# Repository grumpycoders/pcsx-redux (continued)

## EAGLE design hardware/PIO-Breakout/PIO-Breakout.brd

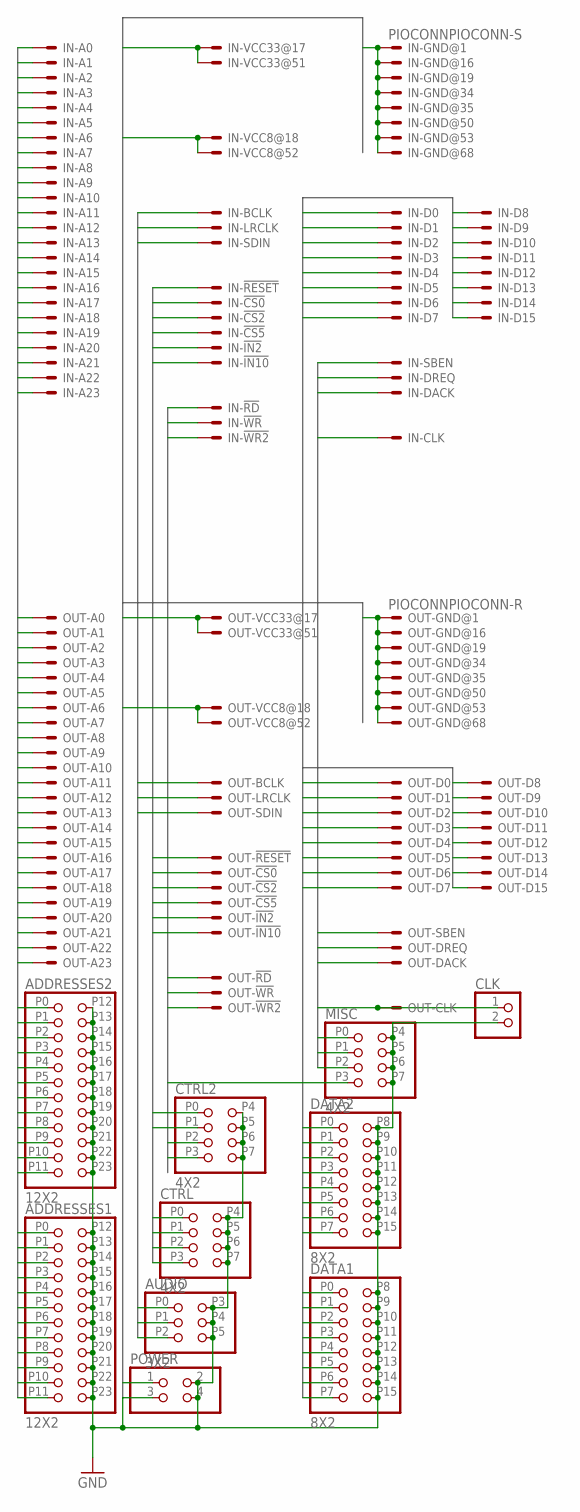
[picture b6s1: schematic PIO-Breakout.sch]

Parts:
ADDRESSES1, ADDRESSES2: 12X2
AUDIO: 3X2
CLK: PINHD-1X2; 1X02
CTRL, CTRL2: 4X2
DATA1, DATA2: 8X2
IN: PIOCONNPIOCONN-S; PIOCONN
MISC: 4X2
OUT: PIOCONNPIOCONN-R; PIOCONN-R
POWER: PINHD-2X2; 2X02

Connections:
+3V3: IN.17, IN.51, OUT.17, OUT.51, POWER.3
+8V: IN.18, IN.52, OUT.18, OUT.52, POWER.1
A0: ADDRESSES1.P11, IN.14, OUT.14
A1: ADDRESSES2.P11, IN.48, OUT.48
A2: ADDRESSES1.P10, IN.15, OUT.15
A3: ADDRESSES2.P10, IN.49, OUT.49
A4: ADDRESSES1.P9, IN.20, OUT.20
A5: ADDRESSES2.P9, IN.54, OUT.54
A6: ADDRESSES1.P8, IN.21, OUT.21
A7: ADDRESSES2.P8, IN.55, OUT.55
A8: ADDRESSES1.P7, IN.22, OUT.22
A9: ADDRESSES2.P7, IN.56, OUT.56
A10: ADDRESSES1.P6, IN.23, OUT.23
A11: ADDRESSES2.P6, IN.57, OUT.57
A12: ADDRESSES1.P5, IN.24, OUT.24
A13: ADDRESSES2.P5, IN.58, OUT.58
A14: ADDRESSES1.P4, IN.25, OUT.25
A15: ADDRESSES2.P4, IN.59, OUT.59
A16: ADDRESSES1.P3, IN.26, OUT.26
A17: ADDRESSES2.P3, IN.60, OUT.60
A18: ADDRESSES1.P2, IN.27, OUT.27
A19: ADDRESSES2.P2, IN.61, OUT.61
A20: ADDRESSES1.P1, IN.28, OUT.28
A21: ADDRESSES2.P1, IN.62, OUT.62
A22: ADDRESSES1.P0, IN.29, OUT.29
A23: ADDRESSES2.P0, IN.63, OUT.63
BCLK: AUDIO.P2, IN.33, OUT.33
CLK: CLK.1, IN.32, OUT.32
CS0: CTRL.P0, IN.4, OUT.4
CS2: CTRL.P1, IN.39, OUT.39
CS5: CTRL2.P0, IN.65, OUT.65
D0: DATA1.P7, IN.6, OUT.6
D1: DATA2.P7, IN.40, OUT.40
D2: DATA1.P6, IN.7, OUT.7
D3: DATA2.P6, IN.41, OUT.41
D4: DATA1.P5, IN.8, OUT.8
D5: DATA2.P5, IN.42, OUT.42
D6: DATA1.P4, IN.9, OUT.9
D7: DATA2.P4, IN.43, OUT.43
D8: DATA1.P3, IN.10, OUT.10
D9: DATA2.P3, IN.44, OUT.44
D10: DATA1.P2, IN.11, OUT.11
D11: DATA2.P2, IN.45, OUT.45
D12: DATA1.P1, IN.12, OUT.12
D13: DATA2.P1, IN.46, OUT.46
D14: DATA1.P0, IN.13, OUT.13
D15: DATA2.P0, IN.47, OUT.47
DACK: IN.36, MISC.P1, OUT.36
DREQ: IN.3, MISC.P2, OUT.3
GND: ADDRESSES1.P12, ADDRESSES1.P13, ADDRESSES1.P14, ADDRESSES1.P15, ADDRESSES1.P16, ADDRESSES1.P17, ADDRESSES1.P18, ADDRESSES1.P19, ADDRESSES1.P20, ADDRESSES1.P21, ADDRESSES1.P22, ADDRESSES1.P23, ADDRESSES2.P12, ADDRESSES2.P13, ADDRESSES2.P14, ADDRESSES2.P15, ADDRESSES2.P16, ADDRESSES2.P17, ADDRESSES2.P18, ADDRESSES2.P19, ADDRESSES2.P20, ADDRESSES2.P21, ADDRESSES2.P22, ADDRESSES2.P23, AUDIO.P3, AUDIO.P4, AUDIO.P5, CLK.2, CTRL.P4, CTRL.P5, CTRL.P6, CTRL.P7, CTRL2.P4, CTRL2.P5, CTRL2.P6, CTRL2.P7, DATA1.P8, DATA1.P9, DATA1.P10, DATA1.P11, DATA1.P12, DATA1.P13, DATA1.P14, DATA1.P15, DATA2.P8, DATA2.P9, DATA2.P10, DATA2.P11, DATA2.P12, DATA2.P13, DATA2.P14, DATA2.P15, IN.1, IN.16, IN.19, IN.34, IN.35, IN.50, IN.53, IN.68, MISC.P4, MISC.P5, MISC.P6, MISC.P7, OUT.1, OUT.16, OUT.19, OUT.34, OUT.35, OUT.50, OUT.53, OUT.68, POWER.2, POWER.4
IN2: CTRL2.P1, IN.31, OUT.31
IN10: CTRL.P2, IN.37, OUT.37
LRCLK: AUDIO.P1, IN.66, OUT.66
RD: CTRL2.P2, IN.30, OUT.30
RESET: CTRL.P3, IN.2, OUT.2
SBEN: IN.5, MISC.P0, OUT.5
SDIN: AUDIO.P0, IN.67, OUT.67
WR: CTRL2.P3, IN.64, OUT.64
WR2: IN.38, MISC.P3, OUT.38

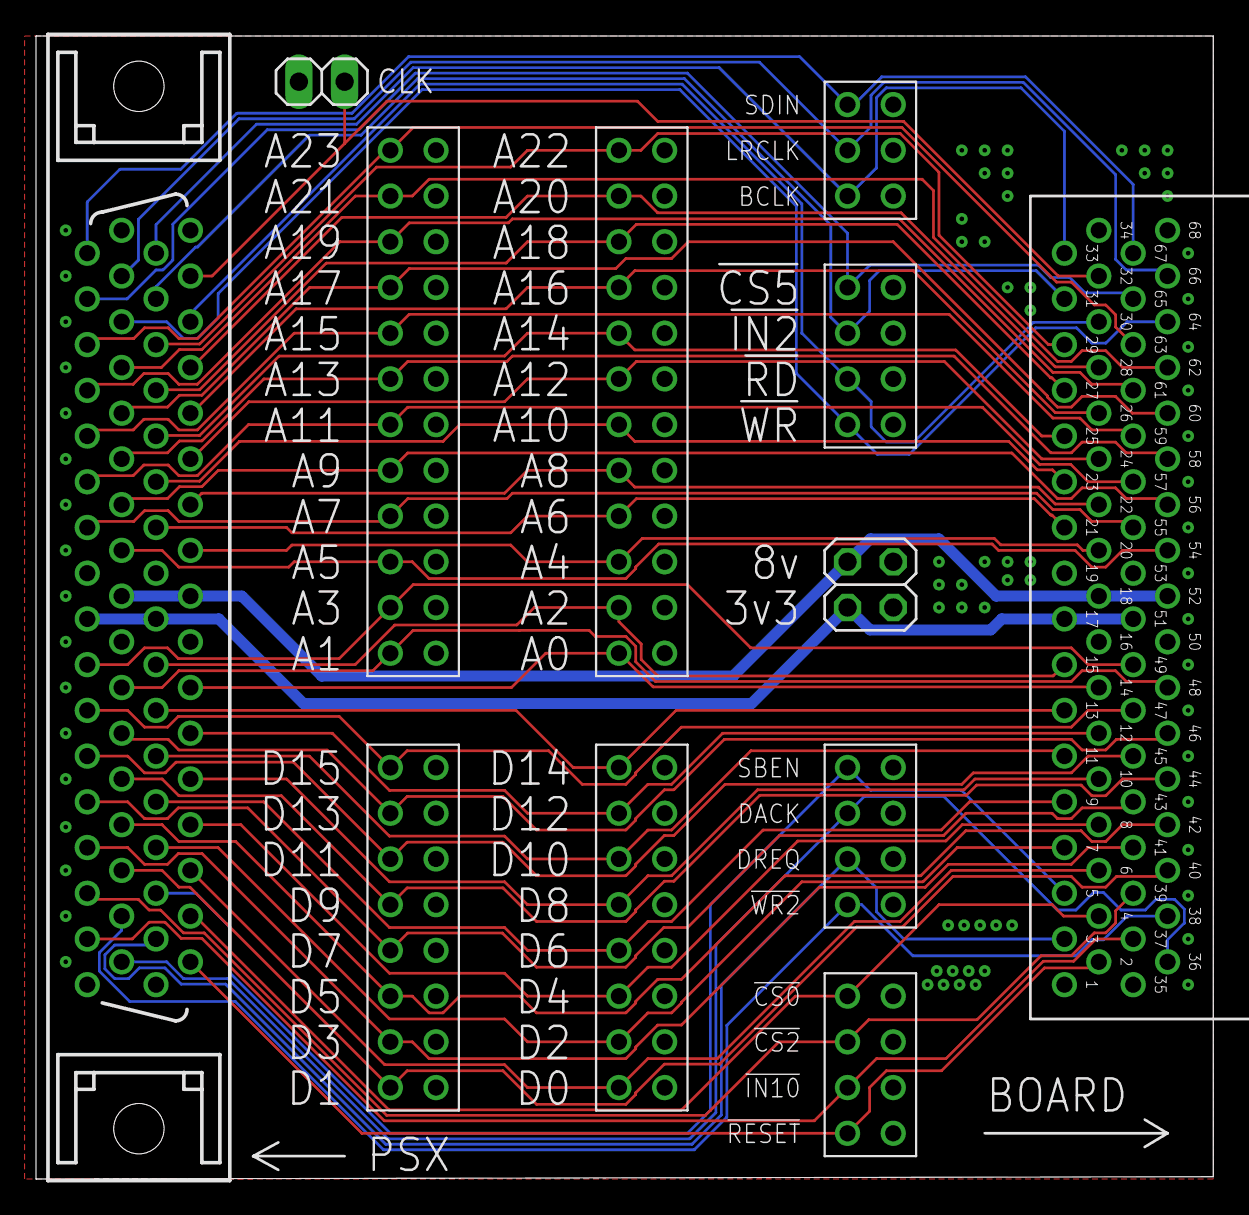
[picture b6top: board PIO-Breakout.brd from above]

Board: 2 copper layers, 65.4 x 63.5 mm, 12 parts (1 on the bottom side), 59 nets.

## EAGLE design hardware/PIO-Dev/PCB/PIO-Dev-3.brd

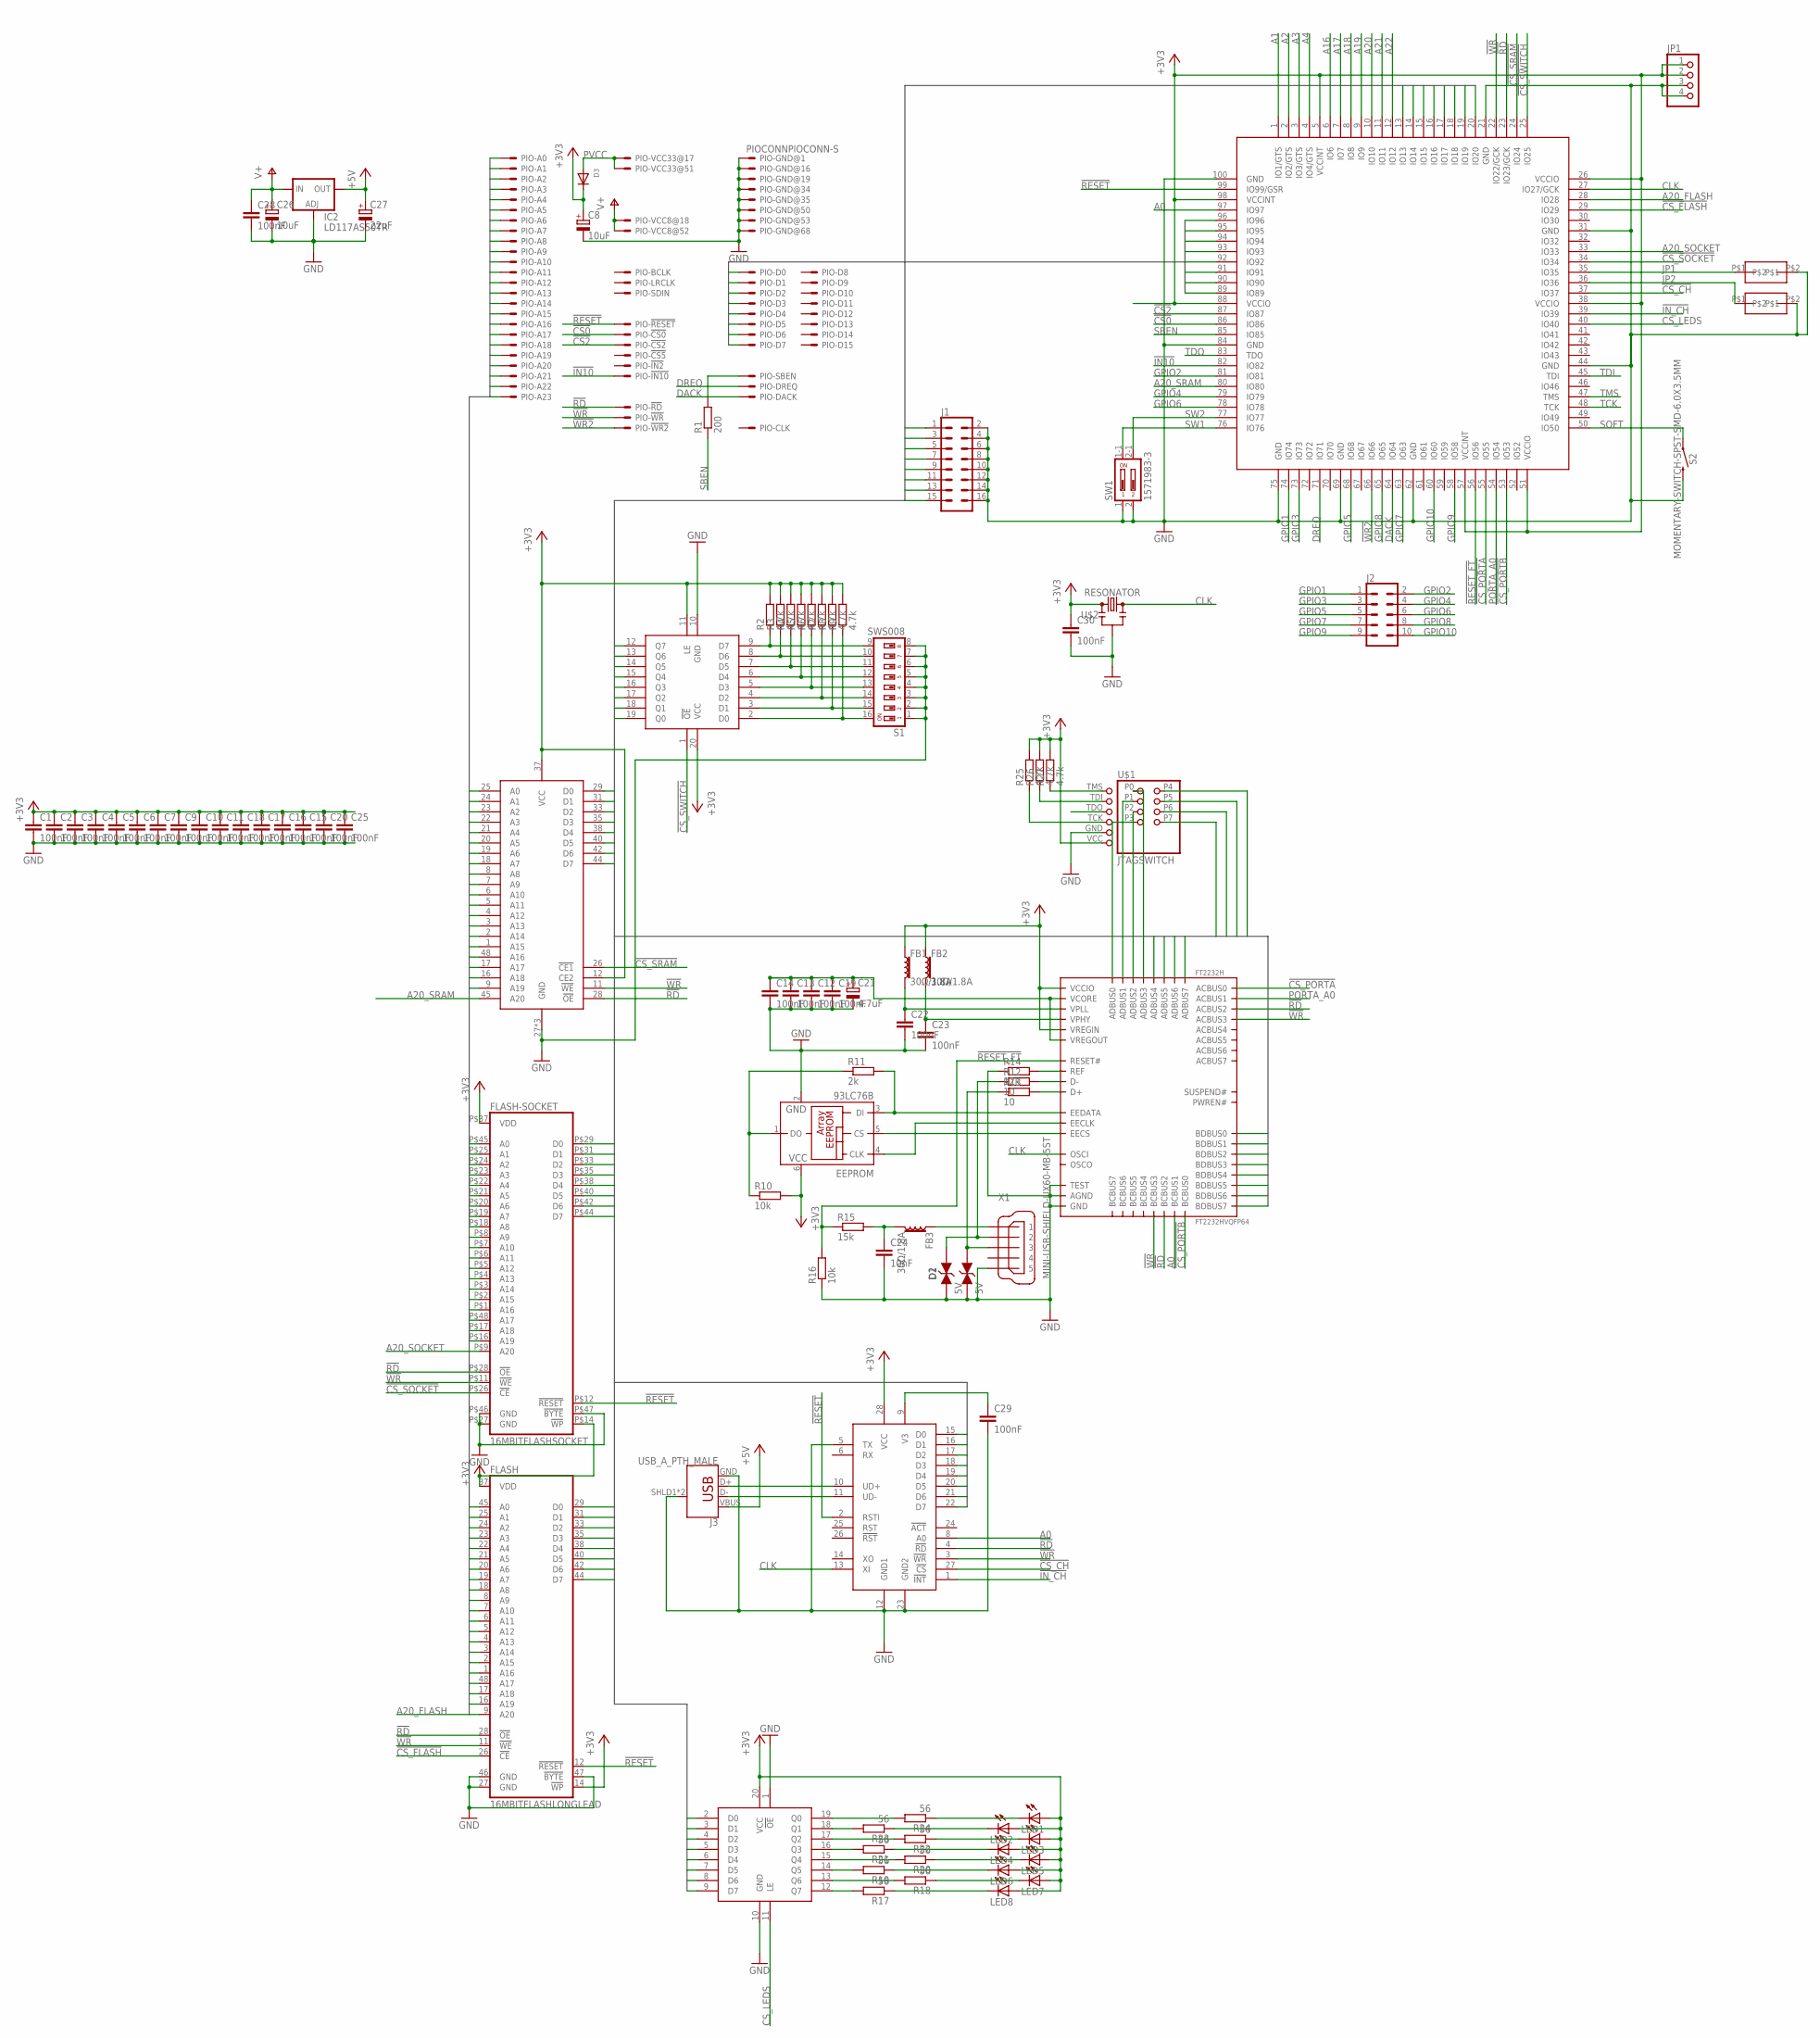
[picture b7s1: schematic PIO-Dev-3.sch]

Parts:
C1, C2, C3, C4, C5, C6, C7, C9, C10, C11, C25, C29: 100nF; C0402K
C8, C26: 10uF; A/3216-18W
C12, C13, C14, C15, C16, C17, C18, C19, C20, C22, C23, C28, C30: 100nF; C0603K
C21: 4.7uF; A/3216-18W
C24: 10nF; C0402K
C27: 22uF; A/3216-18W
CH: CH375B; SOP28-LL
CPLD: XC95144XL-100; TQFP100
D1, D2: 5V; WE-VE_0603
D3: DIODESOD-123; SOD-123
EEPROM: 93LC76B; SOT23-6
FB1, FB2, FB3: 30Ω/1.8A; 0603
FLASH: 16MBITFLASHLONGLEAD; TSOP48-LL
FLASH-SOCKET: 16MBITFLASHSOCKET; TSOP48-ADAPTER
FT2232H: FT2232HVQFP64; VQFP64
IC2: LD117AS50TR; SOT223
J1: CONN_08X2SHD_SMD; 2X8-SHROUDED_SMD
J2: CONN_05X2SHD_SMD; 2X5-SHROUDED_SMD
J3: USB_A_PTH_MALE; USB-A-H
JP1: PINHD-1X4; 1X04
LED1, LED2, LED3, LED4, LED5, LED6, LED7, LED8: LEDCHIPLED_1206; CHIPLED_1206
LEDS: 74LVC573APW; TSSOP20-LL
PIO: PIOCONNPIOCONN-S; PIOCONN
R1: 200; R0402
R2, R3, R4, R5, R6, R7, R8, R9, R25, R26, R27: 4.7k; R0402
R10, R16: 10k; R0402
R11: 2k; R0402
R12, R13: 10; R0402
R14: 12k; R0402
R15: 15k; R0402
R17, R18, R19, R20, R21, R22, R23, R24: 56; R0603
S1: SWS008; SMS-008
S2: MOMENTARY-SWITCH-SPST-SMD-6.0X3.5MM; TACTILE_SWITCH_SMD_6.0X3.5MM
SRAM: CY62167EV30LL; TSOP48-LL
SW1: 1571983-3
SWITCH: 74LVC573APW; TSSOP20-LL
U$1: JTAGSWITCH
U$2: RESONATOR
U$3, U$4: SMD-JUMPER
X1: MINI-USB-SHIELD-UX60-MB-5ST; UX60-MB-5ST

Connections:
!CS0: CPLD.86 (IO86), PIO.4
!CS2: CPLD.87 (IO87), PIO.39
!CS_CH: CH.27 (!CS), CPLD.37 (IO37)
!CS_FLASH: CPLD.29 (IO29), FLASH.26 (!CE)
!CS_PORTA: CPLD.55 (IO55), FT2232H.26 (ACBUS0)
!CS_PORTB: CPLD.53 (IO53), FT2232H.48 (BCBUS0)
!CS_SOCKET: CPLD.34 (IO34), FLASH-SOCKET.P$26 (!CE)
!CS_SRAM: CPLD.24 (IO24), SRAM.26 (!CE1)
!CS_SWITCH: CPLD.25 (IO25), SWITCH.1 (!OE)
!IN10: CPLD.82 (IO82), PIO.37
!IN_CH: CH.1 (!INT), CPLD.39 (IO39)
!RD: CH.4 (!RD), CPLD.23 (IO23/GCK), FLASH.28 (!OE), FLASH-SOCKET.P$28 (!OE), FT2232H.28 (ACBUS2), FT2232H.53 (BCBUS2), PIO.30, SRAM.28 (!OE)
!RESET: CH.2 (RSTI), CPLD.99 (IO99/GSR), FLASH.12 (!RESET), FLASH-SOCKET.P$12 (!RESET), PIO.2
!RESET_FT: CPLD.56 (IO56), FT2232H.14 (RESET#), R15.1, R16.2
!WR: CH.3 (!WR), CPLD.22 (IO22/GCK), FLASH.11 (!WE), FLASH-SOCKET.P$11 (!WE), FT2232H.29 (ACBUS3), FT2232H.54 (BCBUS3), PIO.64, SRAM.11 (!WE)
!WR2: CPLD.66 (IO66), PIO.38
+3V3: C1.1, C2.1, C3.1, C4.1, C5.1, C6.1, C7.1, C8.+, C9.1, C10.1, C11.1, C15.1, C16.1, C17.1, C18.1, C20.1, C25.1, C30.1, CH.28 (VCC), CPLD.5 (VCCINT), CPLD.26 (VCCIO), CPLD.38 (VCCIO), CPLD.51 (VCCIO), CPLD.57 (VCCINT), CPLD.88 (VCCIO), CPLD.98 (VCCINT), D3.C, EEPROM.6 (VCC), FB1.1, FB2.1, FLASH.14 (!WP), FLASH.37 (VDD), FLASH-SOCKET.P$14 (!WP), FLASH-SOCKET.P$37 (VDD), FT2232H.20 (VCCIO), FT2232H.31 (VCCIO), FT2232H.42 (VCCIO), FT2232H.50 (VREGIN), FT2232H.56 (VCCIO), JP1.1, JP1.2, LED1.A, LED2.A, LED3.A, LED4.A, LED5.A, LED6.A, LED7.A, LED8.A, LEDS.20 (VCC), R2.2, R3.2, R4.2, R5.2, R6.2, R7.2, R8.2, R9.2, R10.2, R25.2, R26.2, R27.2, SRAM.12 (CE2), SRAM.37 (VCC), SWITCH.11 (LE), SWITCH.20 (VCC), U$1.VCC, U$2.P4 (VDD)
+5V: C27.+, IC2.4 (OUT), J3.VBUS
A0: CH.8 (A0), CPLD.97 (IO97), FLASH.45 (A0), FLASH-SOCKET.P$45 (A0), FT2232H.52 (BCBUS1), PIO.14, SRAM.25 (A0)
A1: CPLD.1 (IO1/GTS), FLASH.25 (A1), FLASH-SOCKET.P$25 (A1), PIO.48, SRAM.24 (A1)
A2: CPLD.2 (IO2/GTS), FLASH.24 (A2), FLASH-SOCKET.P$24 (A2), PIO.15, SRAM.23 (A2)
A3: CPLD.3 (IO3/GTS), FLASH.23 (A3), FLASH-SOCKET.P$23 (A3), PIO.49, SRAM.22 (A3)
A4: CPLD.4 (IO4/GTS), FLASH.22 (A4), FLASH-SOCKET.P$22 (A4), PIO.20, SRAM.21 (A4)
A5: FLASH.21 (A5), FLASH-SOCKET.P$21 (A5), PIO.54, SRAM.20 (A5)
A6: FLASH.20 (A6), FLASH-SOCKET.P$20 (A6), PIO.21, SRAM.19 (A6)
A7: FLASH.19 (A7), FLASH-SOCKET.P$19 (A7), PIO.55, SRAM.18 (A7)
A8: FLASH.18 (A8), FLASH-SOCKET.P$18 (A8), PIO.22, SRAM.8 (A8)
A9: FLASH.8 (A9), FLASH-SOCKET.P$8 (A9), PIO.56, SRAM.7 (A9)
A10: FLASH.7 (A10), FLASH-SOCKET.P$7 (A10), PIO.23, SRAM.6 (A10)
A11: FLASH.6 (A11), FLASH-SOCKET.P$6 (A11), PIO.57, SRAM.5 (A11)
A12: FLASH.5 (A12), FLASH-SOCKET.P$5 (A12), PIO.24, SRAM.4 (A12)
A13: FLASH.4 (A13), FLASH-SOCKET.P$4 (A13), PIO.58, SRAM.3 (A13)
A14: FLASH.3 (A14), FLASH-SOCKET.P$3 (A14), PIO.25, SRAM.2 (A14)
A15: FLASH.2 (A15), FLASH-SOCKET.P$2 (A15), PIO.59, SRAM.1 (A15)
A16: CPLD.6 (IO6), FLASH.1 (A16), FLASH-SOCKET.P$1 (A16), PIO.26, SRAM.48 (A16)
A17: CPLD.7 (IO7), FLASH.48 (A17), FLASH-SOCKET.P$48 (A17), PIO.60, SRAM.17 (A17)
A18: CPLD.8 (IO8), FLASH.17 (A18), FLASH-SOCKET.P$17 (A18), PIO.27, SRAM.16 (A18)
A19: CPLD.9 (IO9), FLASH.16 (A19), FLASH-SOCKET.P$16 (A19), PIO.61, SRAM.9 (A19)
A20: CPLD.10 (IO10), PIO.28
A20_FLASH: CPLD.28 (IO28), FLASH.9 (A20)
A20_SOCKET: CPLD.33 (IO33), FLASH-SOCKET.P$9 (A20)
A20_SRAM: CPLD.80 (IO80), SRAM.45 (A20)
A21: CPLD.11 (IO11), PIO.62
A22: CPLD.12 (IO12), PIO.29
A23: PIO.63
AD0: FT2232H.16 (ADBUS0), U$1.P3
AD1: FT2232H.17 (ADBUS1), U$1.P1
AD2: FT2232H.18 (ADBUS2), U$1.P2
AD3: FT2232H.19 (ADBUS3), U$1.P0
CDM: CH.11 (UD-), J3.D-
CDP: CH.10 (UD+), J3.D+
CLK: CH.13 (XI), CPLD.27 (IO27/GCK), FT2232H.2 (OSCI), U$2.P3 (OUTPUT)
CS_LEDS: CPLD.40 (IO40), LEDS.11 (LE)
D0: CH.15 (D0), CPLD.20 (IO20), FLASH.29 (D0), FLASH-SOCKET.P$29 (D0), FT2232H.38 (BDBUS0), J1.15, LEDS.2 (D0), SRAM.29 (D0), SWITCH.12 (Q7), U$1.P4
D1: CH.16 (D1), CPLD.19 (IO19), FLASH.31 (D1), FLASH-SOCKET.P$31 (D1), FT2232H.39 (BDBUS1), J1.13, LEDS.3 (D1), SRAM.31 (D1), SWITCH.13 (Q6), U$1.P6
D2: CH.17 (D2), CPLD.18 (IO18), FLASH.33 (D2), FLASH-SOCKET.P$33 (D2), FT2232H.40 (BDBUS2), J1.11, LEDS.4 (D2), SRAM.33 (D2), SWITCH.14 (Q5), U$1.P5
D3: CH.18 (D3), CPLD.17 (IO17), FLASH.35 (D3), FLASH-SOCKET.P$35 (D3), FT2232H.41 (BDBUS3), J1.9, LEDS.5 (D3), SRAM.35 (D3), SWITCH.15 (Q4), U$1.P7
D4: CH.19 (D4), CPLD.16 (IO16), FLASH.38 (D4), FLASH-SOCKET.P$38 (D4), FT2232H.21 (ADBUS4), FT2232H.43 (BDBUS4), J1.7, LEDS.6 (D4), SRAM.38 (D4), SWITCH.16 (Q3)
D5: CH.20 (D5), CPLD.15 (IO15), FLASH.40 (D5), FLASH-SOCKET.P$40 (D5), FT2232H.22 (ADBUS5), FT2232H.44 (BDBUS5), J1.5, LEDS.7 (D5), SRAM.40 (D5), SWITCH.17 (Q2)
D6: CH.21 (D6), CPLD.14 (IO14), FLASH.42 (D6), FLASH-SOCKET.P$42 (D6), FT2232H.23 (ADBUS6), FT2232H.45 (BDBUS6), J1.3, LEDS.8 (D6), SRAM.42 (D6), SWITCH.18 (Q1)
D7: CH.22 (D7), CPLD.13 (IO13), FLASH.44 (D7), FLASH-SOCKET.P$44 (D7), FT2232H.24 (ADBUS7), FT2232H.46 (BDBUS7), J1.1, LEDS.9 (D7), SRAM.44 (D7), SWITCH.19 (Q0)
DACK: CPLD.64 (IO64), PIO.36
DM: D2.1, R12.1, X1.2
DP: D1.1, R13.1, X1.3
DREQ: CPLD.71 (IO71), PIO.3
EECLK: EEPROM.4 (CLK), FT2232H.62 (EECLK)
EECS: EEPROM.5 (CS), FT2232H.63 (EECS)
EEDATA: EEPROM.3 (DI), FT2232H.61 (EEDATA), R11.2
EEDO: EEPROM.1 (DO), R10.1, R11.1
FDM: FT2232H.7 (D-), R12.2
FDP: FT2232H.8 (D+), R13.2
GND: C1.2, C2.2, C3.2, C4.2, C5.2, C6.2, C7.2, C8.-, C9.2, C10.2, C11.2, C12.2, C13.2, C14.2, C15.2, C16.2, C17.2, C18.2, C19.2, C20.2, C21.-, C22.2, C23.2, C24.2, C25.2, C26.-, C27.-, C28.2, C29.2, C30.2, CH.5 (TX), CH.12 (GND1), CH.23 (GND2), CPLD.21 (GND), CPLD.31 (GND), CPLD.44 (GND), CPLD.62 (GND), CPLD.69 (GND), CPLD.75 (GND), CPLD.84 (GND), CPLD.100 (GND), D1.2, D2.2, EEPROM.2 (GND), FLASH.27 (GND), FLASH.46 (GND), FLASH.47 (!BYTE), FLASH-SOCKET.P$27 (GND), FLASH-SOCKET.P$46 (GND), FLASH-SOCKET.P$47 (!BYTE), FT2232H.1 (GND), FT2232H.5 (GND), FT2232H.10 (AGND), FT2232H.11 (GND), FT2232H.13 (TEST), FT2232H.15 (GND), FT2232H.25 (GND), FT2232H.35 (GND), FT2232H.47 (GND), FT2232H.51 (GND), IC2.1 (ADJ), J1.2, J1.4, J1.6, J1.8, J1.10, J1.12, J1.14, J1.16, J3.GND, J3.SHLD1 (SHIELD), J3.SHLD2 (SHIELD), JP1.3, JP1.4, LEDS.1 (!OE), LEDS.10 (GND), PIO.1, PIO.16, PIO.19, PIO.34, PIO.35, PIO.50, PIO.53, PIO.68, R14.1, R16.1, S1.1, S1.2, S1.3, S1.4, S1.5, S1.6, S1.7, S1.8, S2.2, SRAM.27 (GND), SRAM.46 (GND), SRAM.47 (GND), SW1.1, SW1.2, SWITCH.10 (GND), U$1.GND, U$2.P2 (GND), U$3.P$2, U$4.P$2, X1.5
GPIO1: CPLD.74 (IO74), J2.1
GPIO2: CPLD.81 (IO81), J2.2
GPIO3: CPLD.73 (IO73), J2.3
GPIO4: CPLD.79 (IO79), J2.4
GPIO5: CPLD.68 (IO68), J2.5
GPIO6: CPLD.78 (IO78), J2.6
GPIO7: CPLD.63 (IO63), J2.7
GPIO8: CPLD.65 (IO65), J2.8
GPIO9: CPLD.58 (IO58), J2.9
GPIO10: CPLD.60 (IO60), J2.10
JP1: CPLD.35 (IO35), U$3.P$1
JP2: CPLD.36 (IO36), U$4.P$1
L0: LEDS.19 (Q0), R24.2
L1: LEDS.18 (Q1), R23.2
L2: LEDS.17 (Q2), R22.2
L3: LEDS.16 (Q3), R21.2
L4: LEDS.15 (Q4), R20.2
L5: LEDS.14 (Q5), R19.2
L6: LEDS.13 (Q6), R18.2
L7: LEDS.12 (Q7), R17.2
LP0: LED1.C, R24.1
LP1: LED2.C, R23.1
LP2: LED3.C, R22.1
LP3: LED4.C, R21.1
LP4: LED5.C, R20.1
LP5: LED6.C, R19.1
LP6: LED7.C, R18.1
LP7: LED8.C, R17.1
PD0: CPLD.89 (IO89), PIO.6
PD1: CPLD.90 (IO90), PIO.40
PD2: CPLD.91 (IO91), PIO.7
PD3: CPLD.92 (IO92), PIO.41
PD4: CPLD.93 (IO93), PIO.8
PD5: CPLD.94 (IO94), PIO.42
PD6: CPLD.95 (IO95), PIO.9
PD7: CPLD.96 (IO96), PIO.43
PORTA_A0: CPLD.54 (IO54), FT2232H.27 (ACBUS1)
PSBEN: PIO.5, R1.2
PVCC: D3.A, PIO.17, PIO.51
REF: FT2232H.6 (REF), R14.2
S0: R2.1, S1.9, SWITCH.9 (D7)
S1: R3.1, S1.10, SWITCH.8 (D6)
S2: R4.1, S1.11, SWITCH.7 (D5)
S3: R5.1, S1.12, SWITCH.6 (D4)
S4: R6.1, S1.13, SWITCH.5 (D3)
S5: R7.1, S1.14, SWITCH.4 (D2)
S6: R8.1, S1.15, SWITCH.3 (D1)
S7: R9.1, S1.16, SWITCH.2 (D0)
SBEN: CPLD.85 (IO85), R1.1
SOFT: CPLD.50 (IO50), S2.1
SW1: CPLD.76 (IO76), SW1.1-1
SW2: CPLD.77 (IO77), SW1.2-1
TCK: CPLD.48 (TCK), R25.1, U$1.TCK
TDI: CPLD.45 (TDI), R26.1, U$1.TDI
TDO: CPLD.83 (TDO), U$1.TDO
TMS: CPLD.47 (TMS), R27.1, U$1.TMS
V3: C29.1, CH.9 (V3)
V+: C26.+, C28.1, IC2.3 (IN), PIO.18, PIO.52
VBUS: FB3.1, X1.1
VBUSQUIET: C24.1, FB3.2, R15.2
VCORE: C12.1, C13.1, C14.1, C19.1, C21.+, FT2232H.12 (VCORE), FT2232H.37 (VCORE), FT2232H.49 (VREGOUT), FT2232H.64 (VCORE)
VPHY: C23.1, FB2.2, FT2232H.4 (VPHY)
VPLL: C22.1, FB1.2, FT2232H.9 (VPLL)

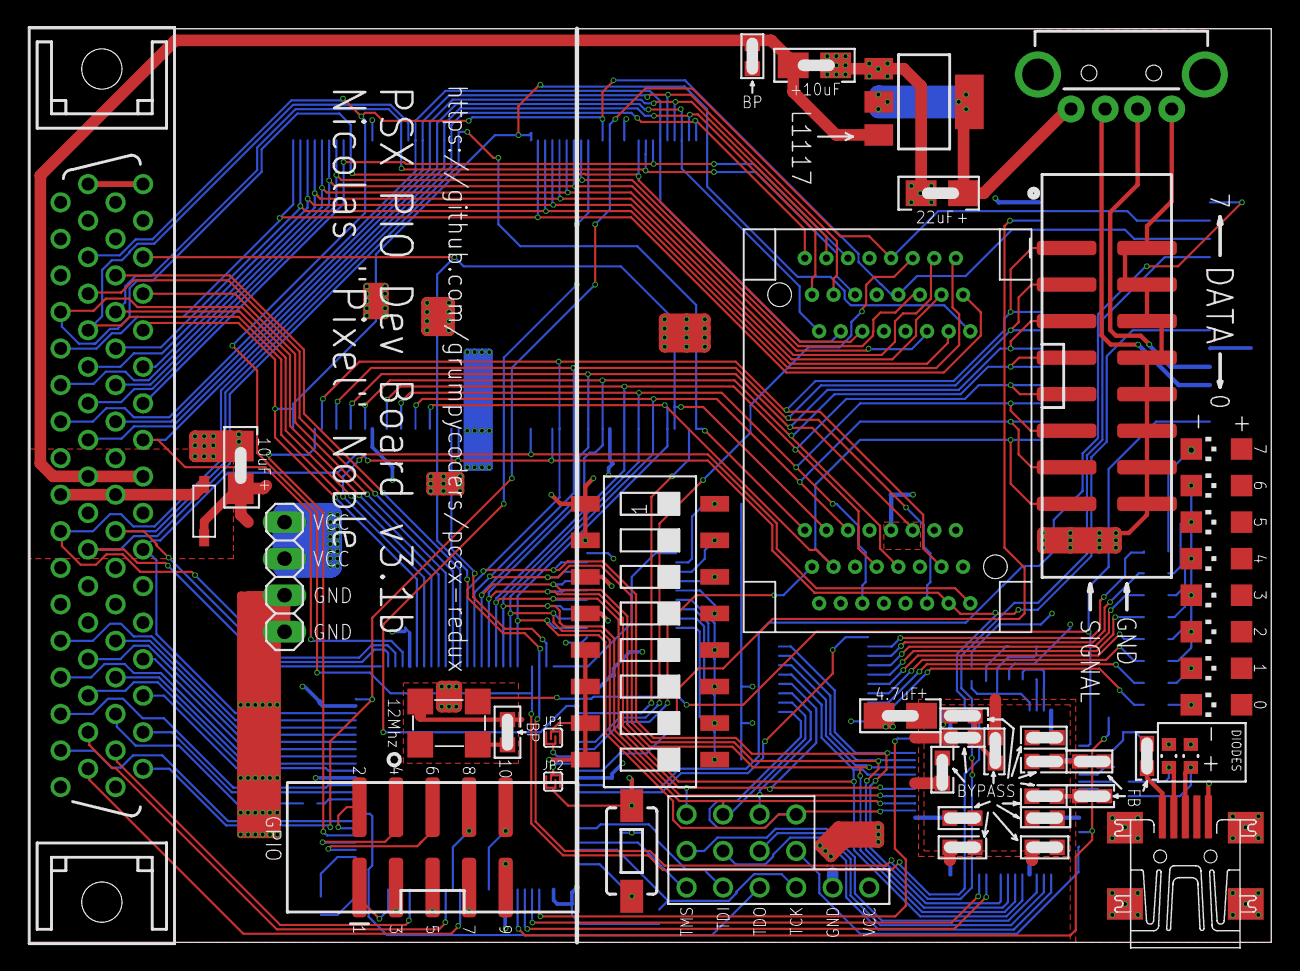
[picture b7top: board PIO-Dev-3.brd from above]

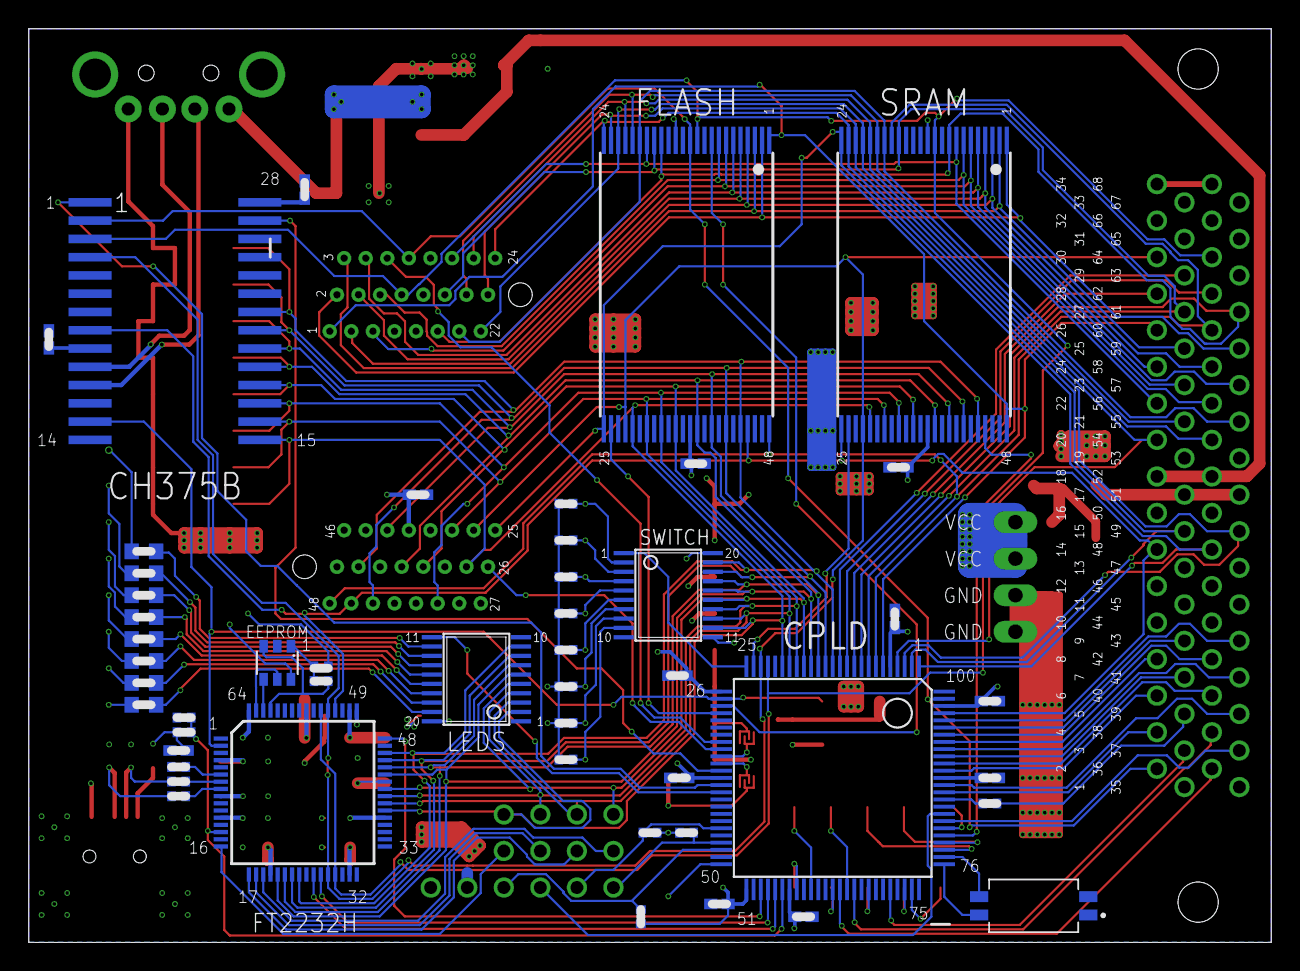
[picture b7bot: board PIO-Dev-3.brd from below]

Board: 2 copper layers, 86.4 x 63.5 mm, 94 parts (49 on the bottom side), 134 nets.

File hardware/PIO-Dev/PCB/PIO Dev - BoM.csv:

Qty,Designator,Footprint,Value,LCSC Part #,DigiKey Part #,Device,Comment
1,GPIO,2X5-SHROUDED_SMD,,C124391,1175-1621-ND,CONN_05X2SHD_SMD,Multi connection point. Often used as Generic Header-pin footprint for 0.1 inch spaced/style header connections
1,DATA,2X8-SHROUDED_SMD,,C192300,1175-1624-ND,CONN_08X2SHD_SMD,Multi connection point. Often used as Generic Header-pin footprint for 0.1 inch spaced/style header connections
1,USBA,PN87520,,C2345,380-1412-ND,PN87520,BERG USB connector
1,MINIUSB,UX60-MB-5ST,MINI-USB-SHIELD-UX60-MB-5ST,C69074,102-4003-1-ND,MINI-USB-SHIELD-UX60-MB-5ST,MINI USB Connector
8,"LED1, LED2, LED3, LED4, LED5, LED6, LED7, LED8",CHIPLED_1206,,C375458,732-4993-1-ND,LEDCHIPLED_1206,LED
12,"C1, C2, C3, C4, C5, C6, C7, C9, C10, C11, C25, C29",C0402,100nF,C1525,399-3520-1-ND,C-EUC0402,"CAPACITOR, European symbol"
2,"C8, C26",A/3216-18W,10uF,C7171,478-13122-1-ND,CPOL-EUA/3216-18W,"POLARIZED CAPACITOR, European symbol"
13,"C12, C13, C14, C15, C16, C17, C18, C19, C20, C22, C23, C28, C30",C0603K,100nF,C14663,399-1095-1-ND,C-EUC0603K,"CAPACITOR, European symbol"
1,C21,A/3216-18W,4.7uF,C7171,478-12949-1-ND,CPOL-EUA/3216-18W,"POLARIZED CAPACITOR, European symbol"
1,C24,C0402,10nF,C15195,399-1279-1-ND,C-EUC0402,"CAPACITOR, European symbol"
1,C27,A/3216-18W,22uF,C7171,399-3692-1-ND,CPOL-EUA/3216-18W,"POLARIZED CAPACITOR, European symbol"
1,SWITCHES2,,,C40735,CKN9064-ND,1571983-3,SWITCH SLIDE DIP SPST 25MA 24V
1,SWITCHES8,,SWS008,C54953,1-1825058-9-ND,SWS008,SMD Dip Switch 8 pol.
1,SW,SMD_6.0X3.5MM,,C136740,CKN12309-1-ND,MOMENTARY-SWITCH-SPST-SMD-6.0X3.5MM,Momentary Switch (Pushbutton) - SPST
1,R1,R0402,200Ω,C25087,311-2253-1-ND,R-EU_R0402,"RESISTOR, European symbol"
11,"R2, R3, R4, R5, R6, R7, R8, R9, R25, R26, R27",R0402,4.7kΩ,C25900,YAG3347CT-ND,R-EU_R0402,"RESISTOR, European symbol"
1,R11,R0402,2kΩ,C4109,YAG3345CT-ND,R-EU_R0402,"RESISTOR, European symbol"
2,"R10, R16",R0402,10k,C25744,YAG1233CT-ND,R-EU_R0402,"RESISTOR, European symbol"
2,"R12, R13",R0402,10Ω,C25077,311-10UCT-ND,R-EU_R0402,"RESISTOR, European symbol"
1,R14,R0402,12k,C25752,311-2224-1-ND,R-EU_R0402,"RESISTOR, European symbol"
1,R15,R0402,15k,C25756,YAG5930CT-ND,R-EU_R0402,"RESISTOR, European symbol"
8,"R17, R18, R19, R20, R21, R22, R23, R24",R0603,56Ω,C25196,311-56UCT-ND,R-EU_R0603,"RESISTOR, European symbol"
3,"FB1, FB2, FB3",603,600Ω/0.5A,C19330,MH1608-601YCT-ND,FERRITE_BEAD-0603,"Ferrite Bead (blocks, cores, rings, chokes, etc.)"
2,"D1, D2",603,5V,C142698,F4239CT-ND,PGB1010603,WE-VE ESD Suppressor
1,D3,SOD-123,,C8598,SM5817PL-TPMSCT-ND,SCHOTTKY DIODE,
2,"LEDS, SWITCH",TSSOP20-LL,74LVC573APW,C6096,1727-6471-ND,74LVC573APW,
1,CLOCK,SMD_5.0X3.2MM,12MHZ,C70689,XC3100CT-ND,OSCILLATOR,
1,EEPROM,SOT23-6,93LC56B,C190271,93LC56BT-I/OTCT-ND,93LC76B,8K Microwire Compatible Serial EEPROM
1,CH,SOP28-LL,CH375B,C8962,n/a,CH375B,
1,SRAM,TSOP48-LL,CY62167EV30LL,C115715,2015-CY62167G30-45ZXI-ND,CY62167EV30LL,
1,FT,VQFP64,FT2232HVQFP64,C27882,768-1024-1-ND,FT2232HVQFP64,
1,REGULATOR,SOT223,LD117AS50TR,C6186,497-6447-1-ND,LD117AS50TR,Low drop fixed and adjustable positive voltage regulators 1 A
1,FLASH,TSOP48-LL,S29AL016J70TFI020,C18276,428-4188-ND,S29AL016J70TFI020,
1,CPLD,TQFP100,XC95144XL-100,C45126,122-1372-ND,XC95144XL-100,

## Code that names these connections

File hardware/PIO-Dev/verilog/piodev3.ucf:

NET "A1" LOC="P1";
NET "A2" LOC="P2";
NET "A3" LOC="P3";
NET "A4" LOC="P4";

NET "A16" LOC="P6";
NET "A17" LOC="P7";
NET "A18" LOC="P8";
NET "A19" LOC="P9";
NET "A20" LOC="P10";
NET "A21" LOC="P11";
NET "A22" LOC="P12";

NET "D<7>" LOC="P13";
NET "D<6>" LOC="P14";
NET "D<5>" LOC="P15";
NET "D<4>" LOC="P16";
NET "D<3>" LOC="P17";
NET "D<2>" LOC="P18";
NET "D<1>" LOC="P19";
NET "D<0>" LOC="P20";

NET "nWR" LOC="P22" | BUFG="CLK";
NET "nRD" LOC="P23" | BUFG="CLK";
NET "nCS_SRAM" LOC="P24";
NET "nCS_SWITCH" LOC="P25";

NET "CLK" LOC="P27" | BUFG="CLK";

NET "A20_FLASH" LOC="P28";
NET "nCS_FLASH" LOC="P29";
NET "A20_SOCKET" LOC="P33";
NET "nCS_SOCKET" LOC="P34";

NET "JP1" LOC="P35";
NET "JP2" LOC="P36";

NET "nCS_CH" LOC="P37";
NET "nIN_CH" LOC="P39";
NET "CS_LEDS" LOC="P40";

NET "SOFT" LOC="P50";

NET "nCS_PORTB" LOC="P53";
NET "A0_PORTA" LOC="P54";
NET "nCS_PORTA" LOC="P55";
NET "nRESET_FT" LOC="P56";

NET "GPIO<9>" LOC="P58";
NET "GPIO<10>" LOC="P60";
NET "GPIO<7>" LOC="P63";

NET "DACK" LOC="P64";

NET "GPIO<8>" LOC="P65";

NET "nWR2" LOC="P66";

NET "GPIO<5>" LOC="P68";

NET "DREQ" LOC="P71";

NET "GPIO<3>" LOC="P73";
NET "GPIO<1>" LOC="P74";

NET "SW1" LOC="P76";
NET "SW2" LOC="P77";

NET "GPIO<6>" LOC="P78";
NET "GPIO<4>" LOC="P79";

NET "A20_SRAM" LOC="P80";

NET "GPIO<2>" LOC="P81";

NET "nIN10" LOC="P82";

NET "SBEN" LOC="P85";

NET "nCS0" LOC="P86";
NET "nCS2" LOC="P87";

NET "PD<0>" LOC="P89";
NET "PD<1>" LOC="P90";
NET "PD<2>" LOC="P91";
NET "PD<3>" LOC="P92";
NET "PD<4>" LOC="P93";
NET "PD<5>" LOC="P94";
NET "PD<6>" LOC="P95";
NET "PD<7>" LOC="P96";

NET "A0" LOC="P97";

NET "nRESET" LOC="P99";
